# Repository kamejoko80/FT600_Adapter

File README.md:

# FT600_Adapter
FT600 adapter hw design with Kicad

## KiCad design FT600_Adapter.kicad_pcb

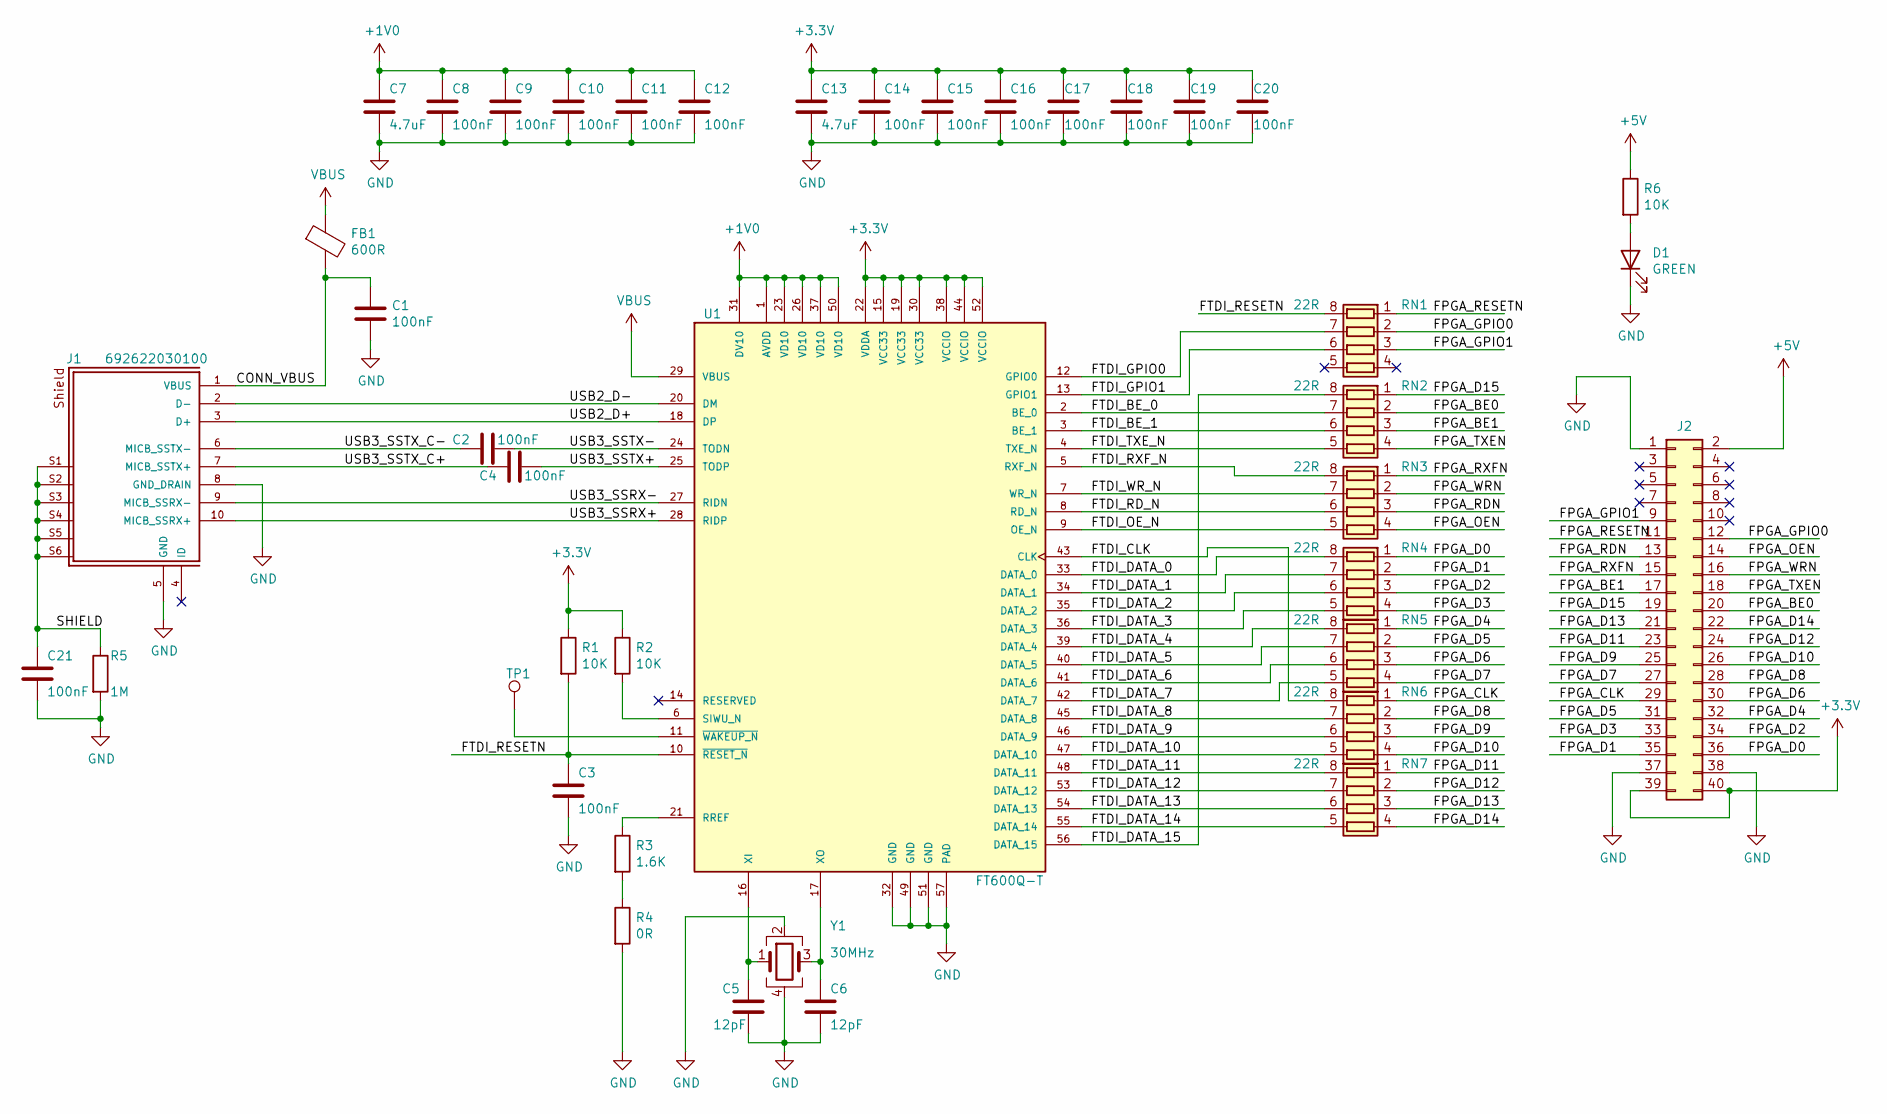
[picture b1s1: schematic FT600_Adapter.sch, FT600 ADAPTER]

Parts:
C1, C2, C3, C4, C8, C9, C10, C11, C12, C14, C15, C16, C17, C18, C19, C20, C21: 100nF; C_0402_1005Metric; Part GCM155R71C104KA55D
C5, C6: 12pF; C_0402_1005Metric; Part AC0402JRNPO9BN120
C7, C13: 4.7uF; C_0603_1608Metric; Part CL10A475KP8NNNC
D1: GREEN; LED_0603_1608Metric
FB1: 600R; L_0603_1608Metric
J1: 692622030100; PART-NUMBER 692622030100
J2: Conn_02x20_Odd_Even; PinSocket_2x20_P2.54mm_Vertical
R1, R2, R6: 10K; R_0402_1005Metric
R3: 1.6K; R_0402_1005Metric
R4: 0R; R_0402_1005Metric
R5: 1M; R_0402_1005Metric
RN1, RN2, RN3, RN4, RN5, RN6, RN7: 22R; R_Array_Convex_4x0402; Part YC124-FR-0722RL
TP1: TestPoint; TestPoint_Pad_1.0x1.0mm
U1: FT600Q-T; QFN40P700X700X85-57N
Y1: 30MHz; Crystal_SMD_3225-4Pin_3.2x2.5mm; Part LFXTAL055962Reel

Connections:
+1V0: C7.1, C8.1, C9.1, C10.1, C11.1, C12.1, U1.1 (AVDD), U1.23 (VD10), U1.26 (VD10), U1.31 (DV10), U1.37 (VD10), U1.50 (VD10)
+3V3: C13.1, C14.1, C15.1, C16.1, C17.1, C18.1, C19.1, C20.1, J2.39, J2.40, R1.1, R2.1, U1.15 (VCC33), U1.19 (VCC33), U1.22 (VDDA), U1.30 (VCC33), U1.38 (VCCIO), U1.44 (VCCIO), U1.52 (VCCIO)
+5V: J2.2, R6.1
/CONN_VBUS: C1.1, FB1.2, J1.1 (VBUS)
/FPGA_BE0: J2.20, RN2.2 (R2.1)
/FPGA_BE1: J2.17, RN2.3 (R3.1)
/FPGA_CLK: J2.29, RN6.1 (R1.1)
/FPGA_D0: J2.36, RN4.1 (R1.1)
/FPGA_D1: J2.35, RN4.2 (R2.1)
/FPGA_D2: J2.34, RN4.3 (R3.1)
/FPGA_D3: J2.33, RN4.4 (R4.1)
/FPGA_D4: J2.32, RN5.1 (R1.1)
/FPGA_D5: J2.31, RN5.2 (R2.1)
/FPGA_D6: J2.30, RN5.3 (R3.1)
/FPGA_D7: J2.27, RN5.4 (R4.1)
/FPGA_D8: J2.28, RN6.2 (R2.1)
/FPGA_D9: J2.25, RN6.3 (R3.1)
/FPGA_D10: J2.26, RN6.4 (R4.1)
/FPGA_D11: J2.23, RN7.1 (R1.1)
/FPGA_D12: J2.24, RN7.2 (R2.1)
/FPGA_D13: J2.21, RN7.3 (R3.1)
/FPGA_D14: J2.22, RN7.4 (R4.1)
/FPGA_D15: J2.19, RN2.1 (R1.1)
/FPGA_GPIO0: J2.12, RN1.2 (R2.1)
/FPGA_GPIO1: J2.9, RN1.3 (R3.1)
/FPGA_OEN: J2.14, RN3.4 (R4.1)
/FPGA_RDN: J2.13, RN3.3 (R3.1)
/FPGA_RESETN: J2.11, RN1.1 (R1.1)
/FPGA_RXFN: J2.15, RN3.1 (R1.1)
/FPGA_TXEN: J2.18, RN2.4 (R4.1)
/FPGA_WRN: J2.16, RN3.2 (R2.1)
/FTDI_BE_0: RN2.7 (R2.2), U1.2 (BE_0)
/FTDI_BE_1: RN2.6 (R3.2), U1.3 (BE_1)
/FTDI_CLK: RN6.8 (R1.2), U1.43 (CLK)
/FTDI_DATA_0: RN4.8 (R1.2), U1.33 (DATA_0)
/FTDI_DATA_1: RN4.7 (R2.2), U1.34 (DATA_1)
/FTDI_DATA_2: RN4.6 (R3.2), U1.35 (DATA_2)
/FTDI_DATA_3: RN4.5 (R4.2), U1.36 (DATA_3)
/FTDI_DATA_4: RN5.8 (R1.2), U1.39 (DATA_4)
/FTDI_DATA_5: RN5.7 (R2.2), U1.40 (DATA_5)
/FTDI_DATA_6: RN5.6 (R3.2), U1.41 (DATA_6)
/FTDI_DATA_7: RN5.5 (R4.2), U1.42 (DATA_7)
/FTDI_DATA_8: RN6.7 (R2.2), U1.45 (DATA_8)
/FTDI_DATA_9: RN6.6 (R3.2), U1.46 (DATA_9)
/FTDI_DATA_10: RN6.5 (R4.2), U1.47 (DATA_10)
/FTDI_DATA_11: RN7.8 (R1.2), U1.48 (DATA_11)
/FTDI_DATA_12: RN7.7 (R2.2), U1.53 (DATA_12)
/FTDI_DATA_13: RN7.6 (R3.2), U1.54 (DATA_13)
/FTDI_DATA_14: RN7.5 (R4.2), U1.55 (DATA_14)
/FTDI_DATA_15: RN2.8 (R1.2), U1.56 (DATA_15)
/FTDI_GPIO0: RN1.7 (R2.2), U1.12 (GPIO0)
/FTDI_GPIO1: RN1.6 (R3.2), U1.13 (GPIO1)
/FTDI_OE_N: RN3.5 (R4.2), U1.9 (OE_N)
/FTDI_RD_N: RN3.6 (R3.2), U1.8 (RD_N)
/FTDI_RESETN: C3.1, R1.2, RN1.8 (R1.2), U1.10 (~RESET_N)
/FTDI_RXF_N: RN3.8 (R1.2), U1.5 (RXF_N)
/FTDI_TXE_N: RN2.5 (R4.2), U1.4 (TXE_N)
/FTDI_WR_N: RN3.7 (R2.2), U1.7 (WR_N)
/SHIELD: C21.1, J1.S1, J1.S2, J1.S3, J1.S4, J1.S5, J1.S6, R5.1
/USB2_D+: J1.3 (D+), U1.18 (DP)
/USB2_D-: J1.2 (D-), U1.20 (DM)
/USB3_SSRX+: J1.10 (MICB_SSRX+), U1.28 (RIDP)
/USB3_SSRX-: J1.9 (MICB_SSRX-), U1.27 (RIDN)
/USB3_SSTX+: C4.1, U1.25 (TODP)
/USB3_SSTX-: C2.1, U1.24 (TODN)
/USB3_SSTX_C+: C4.2, J1.7 (MICB_SSTX+)
/USB3_SSTX_C-: C2.2, J1.6 (MICB_SSTX-)
GND: C1.2, C3.2, C5.2, C6.2, C7.2, C8.2, C9.2, C10.2, C11.2, C12.2, C13.2, C14.2, C15.2, C16.2, C17.2, C18.2, C19.2, C20.2, C21.2, D1.1 (K), J1.5 (GND), J1.8 (GND_DRAIN), J2.1, J2.37, J2.38, R4.2, R5.2, U1.32 (GND), U1.49 (GND), U1.51 (GND), U1.57 (PAD), Y1.2, Y1.4
unnamed: C5.1, U1.16 (XI), Y1.1
unnamed: C6.1, U1.17 (XO), Y1.3
unnamed: D1.2 (A), R6.2
unnamed: R2.2, U1.6 (SIWU_N)
unnamed: R3.1, U1.21 (RREF)
unnamed: R3.2, R4.1
unnamed: TP1.1, U1.11 (~WAKEUP_N)
VBUS: FB1.1, U1.29 (VBUS)

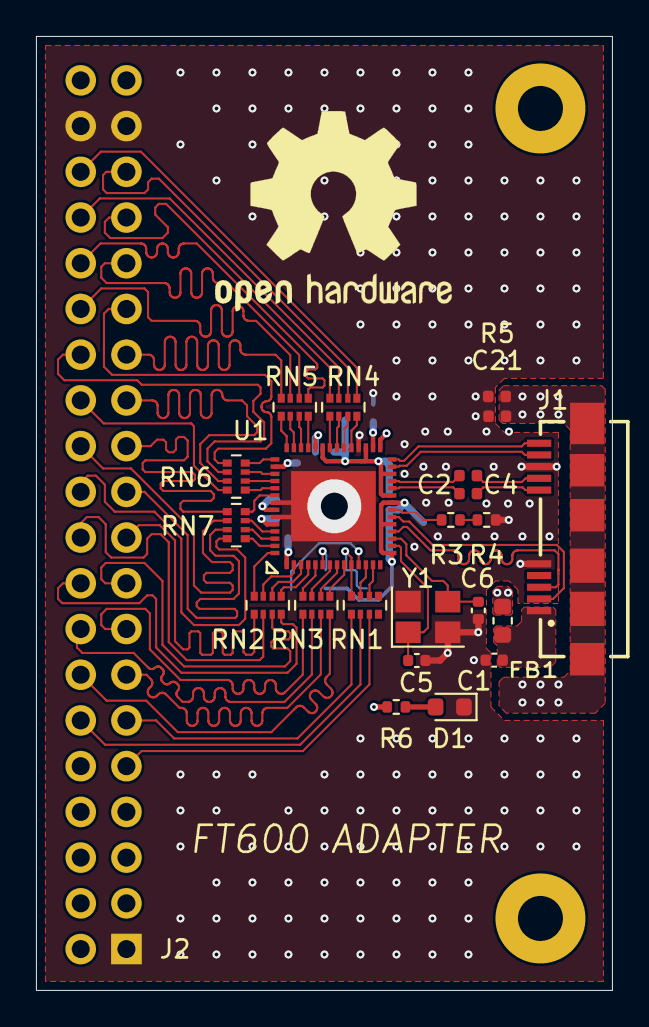
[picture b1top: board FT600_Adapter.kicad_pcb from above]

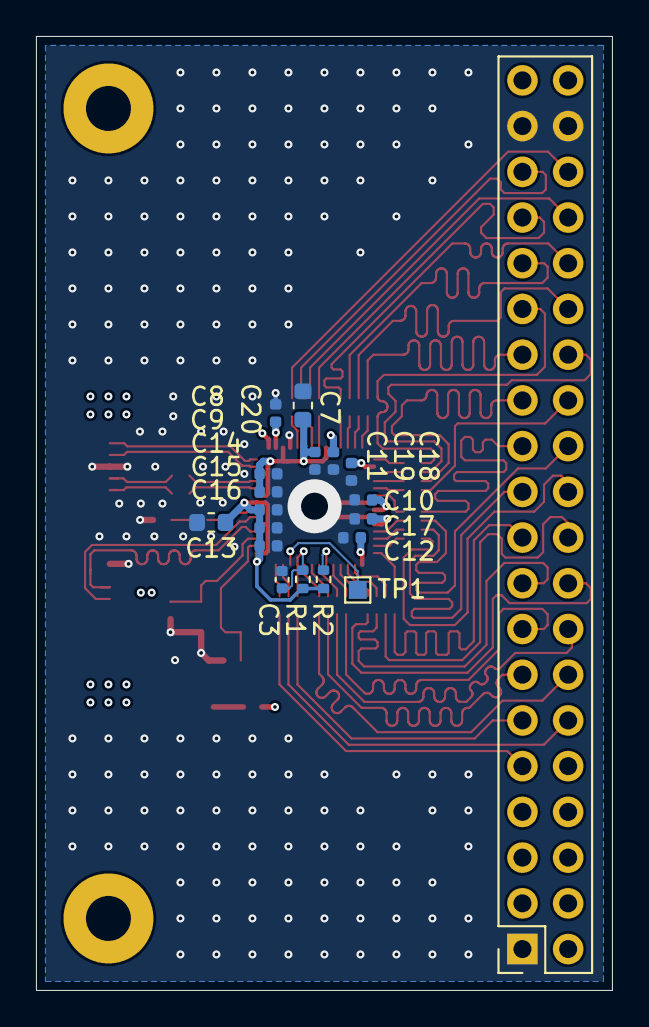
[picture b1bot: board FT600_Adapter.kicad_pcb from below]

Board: 4 copper layers, 32.0 x 53.0 mm, 41 parts (19 on the bottom side), 76 nets.

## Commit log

2020-12-28 Added intial project
2020-12-29 Updated USB3.0 connector
2021-01-01 Updated PCB layout
2021-01-01 Removed unused nets
2021-01-03 Added GND array vias, stand off through holes
2021-01-03 Generated gerber files
2021-01-08 Update components refdes
